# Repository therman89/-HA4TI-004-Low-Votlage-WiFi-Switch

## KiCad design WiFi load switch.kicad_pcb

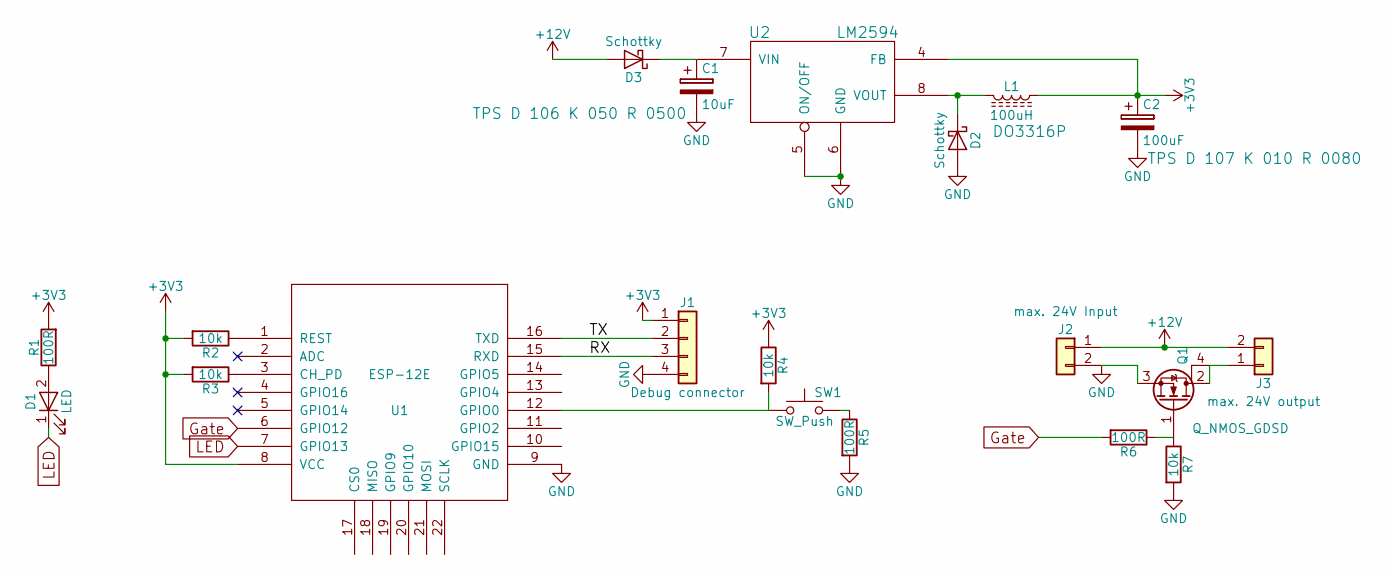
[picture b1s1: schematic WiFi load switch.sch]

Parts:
C1: 10uF; CP_EIA-7343-31_Kemet-D_Pad2.23x2.60mm_HandSolder
C2: 100uF; CP_EIA-7343-31_Kemet-D_Pad2.23x2.60mm_HandSolder; Part number TPS D 107 K 010 R 0080
D1: LED; LED_0603_1608Metric_Castellated
D2, D3: Schottky; D_SOD-123F
J1: Debug connector; PinHeader_1x04_P2.54mm_Vertical
J2: max. 24V Input; TerminalBlock_Altech_AK300-2_P5.00mm
J3: max. 24V output; TerminalBlock_Altech_AK300-2_P5.00mm
L1: 100uH; DO3316P; Part number DO3316P
Q1: Q_NMOS_GDSD; SOT-223
R1, R5, R6: 100R; R_0603_1608Metric_Pad0.84x1.00mm_HandSolder
R2, R3, R4, R7: 10k; R_0603_1608Metric_Pad0.84x1.00mm_HandSolder
SW1: SW_Push; SW_SPST_PTS645
U1: ESP-12E; ESP-12E_SMD
U2: LM2594; SOIC-8_3.9x4.9mm_P1.27mm; Part number TPS D 106 K 050 R 0500

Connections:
+3V3: C2.1, J1.1, L1.1, R1.2, R2.2, R3.2, R4.1, U1.8 (VCC), U2.4 (FB)
+12V: D3.2 (A), J2.1, J3.2
/RX: J1.3, U1.15 (RXD)
/TX: J1.2, U1.16 (TXD)
GND: C1.2, C2.2, D2.2 (A), J1.4, J2.2, Q1.3 (S), R5.2, R7.2, U1.9 (GND), U2.5 (ON/OFF), U2.6 (GND)
Gate: R6.2, U1.6 (GPIO12)
LED: D1.1 (K), U1.7 (GPIO13)
unnamed: C1.1, D3.1 (K), U2.7 (VIN)
unnamed: D1.2 (A), R1.1
unnamed: D2.1 (K), L1.2, U2.8 (VOUT)
unnamed: J3.1, Q1.2 (D), Q1.4 (D)
unnamed: Q1.1 (G), R6.1, R7.1
unnamed: R2.1, U1.1 (REST)
unnamed: R3.1, U1.3 (CH_PD)
unnamed: R4.2, SW1.1, U1.12 (GPIO0)
unnamed: R5.1, SW1.2

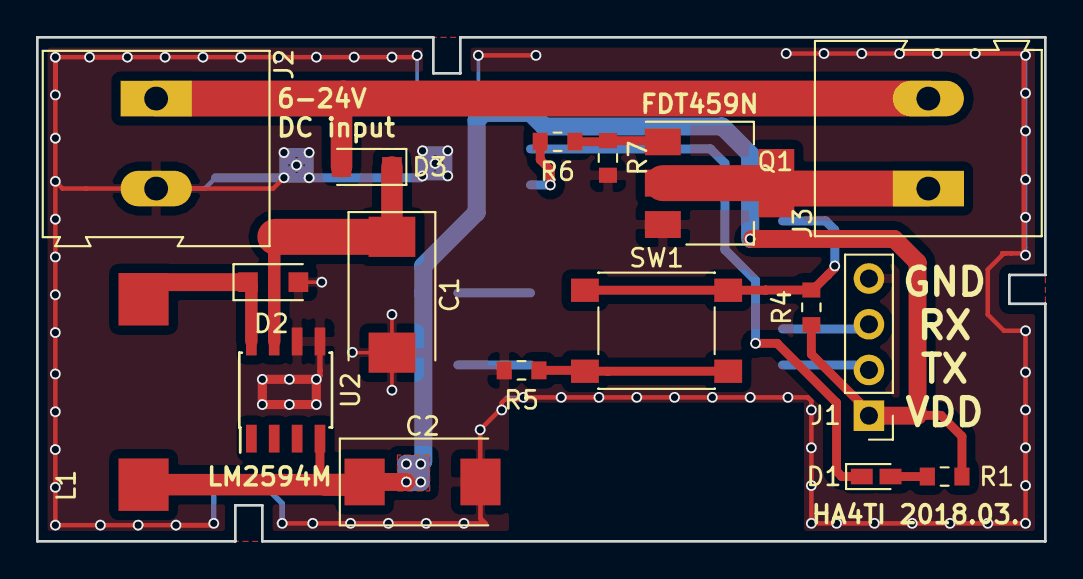
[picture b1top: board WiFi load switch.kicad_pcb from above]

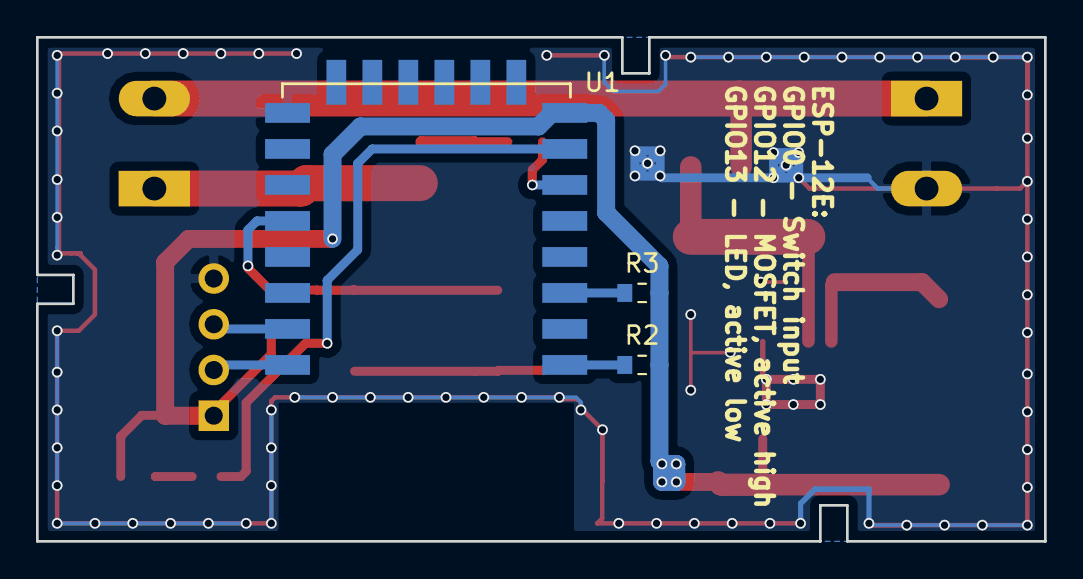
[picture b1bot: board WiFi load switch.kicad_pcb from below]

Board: 2 copper layers, 56.0 x 28.0 mm, 20 parts (3 on the bottom side), 16 nets.

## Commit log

2018-03-22 Initial commit. Preliminary schematic and layout
2018-03-22 Completed layout. Need to consider housing.
2018-03-29 Minor changes. Design was sent to PCB manufacturer
